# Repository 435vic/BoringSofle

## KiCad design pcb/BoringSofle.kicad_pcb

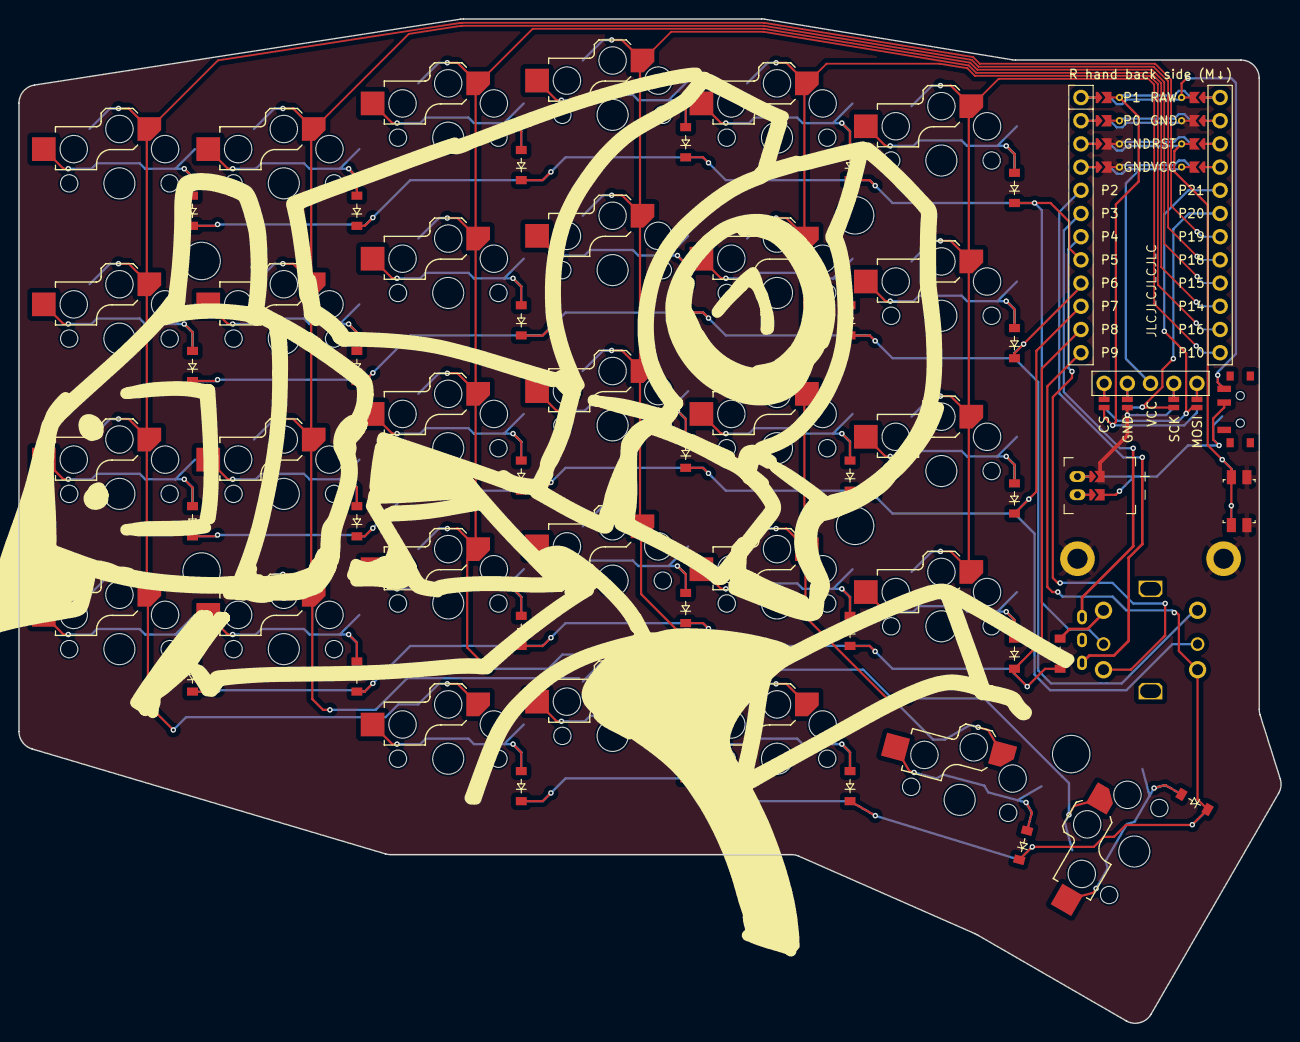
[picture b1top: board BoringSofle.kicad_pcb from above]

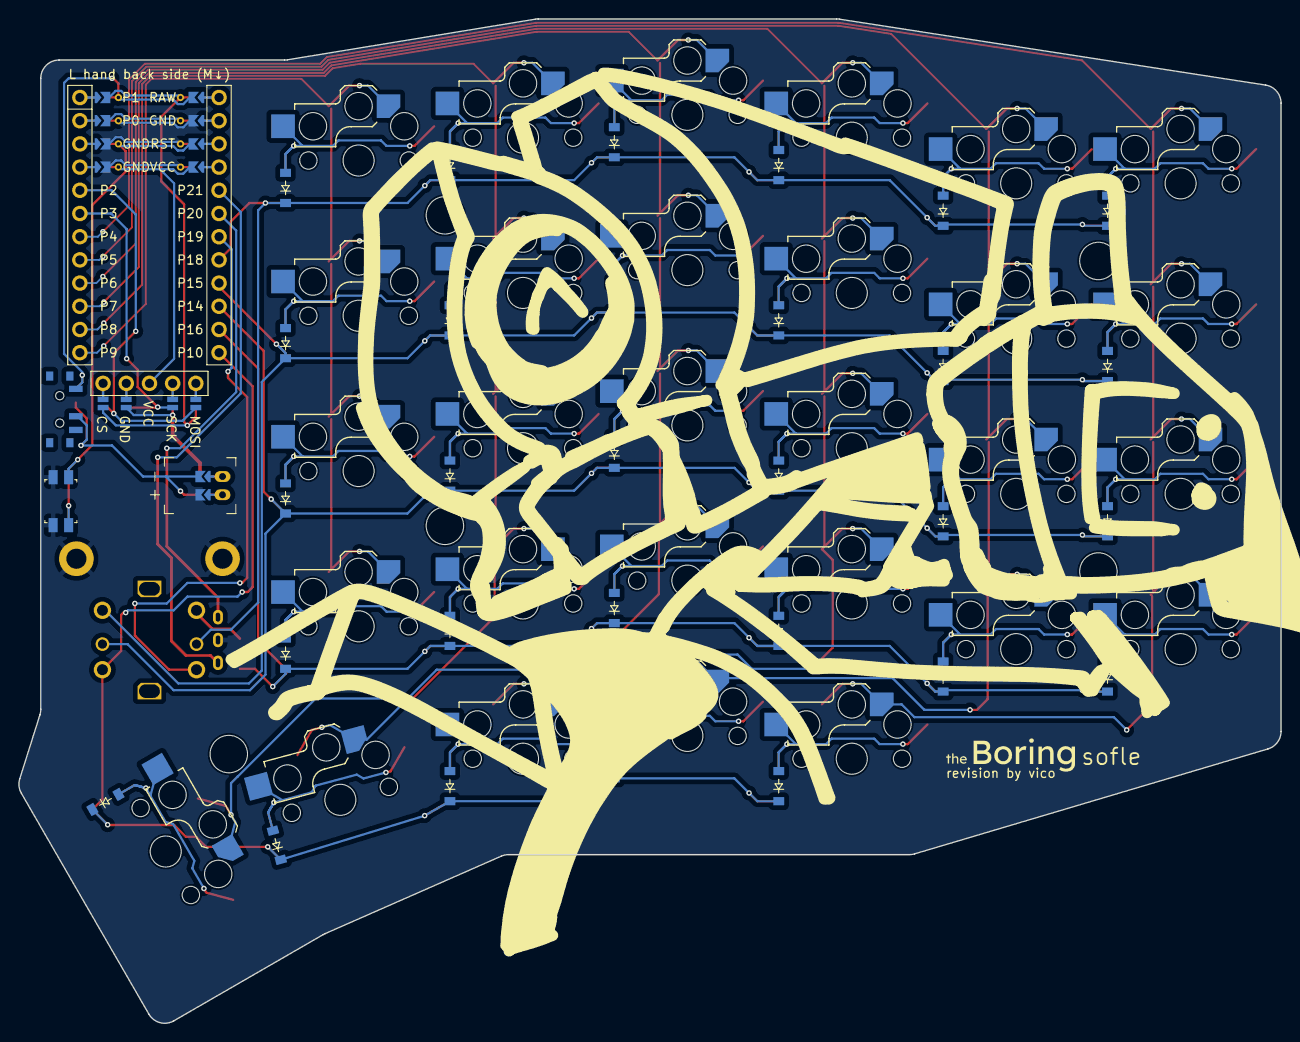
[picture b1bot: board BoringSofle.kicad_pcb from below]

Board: 2 copper layers, 138.2 x 110.0 mm, 73 parts (30 on the bottom side), 58 nets.

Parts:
D1, D2, D3, D4, D5, D6, D7, D8, D9, D10, D11, D12, D13, D14, D15, D16, D17, D18, D19, D20, D21, D22, D23, D24, D25, D26, D27, D28, D29, D30: diode_tht_sod123
DISP1: display_nice_view
H1, H2: mounting_hole_plated
JST1: battery_connector_jst_ph_2
MCU1: mcu_nice_nano
MH1, MH2, MH3, MH4, MH5: mounting_hole_npth
PWR1: power_switch_smd_side
RE1: rotary_encoder_ec11_ec12
RST1: reset_switch_smd_side
S1, S2, S3, S4, S5, S6, S7, S8, S9, S10, S11, S12, S13, S14, S15, S16, S17, S18, S19, S20, S21, S22, S23, S24, S25, S26, S27, S28, S29: switch_choc_v1_v2
SW1: sqku_5way_nav_switch

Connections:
BAT_P: JST1.1, PWR1.2
CS: DISP1.10, DISP1.20, MCU1.124
DISP1_1: DISP1.1, DISP1.14, DISP1.27
DISP1_2: DISP1.2, DISP1.15, DISP1.26
DISP1_4: DISP1.4, DISP1.16, DISP1.25
DISP1_5: DISP1.5, DISP1.17, DISP1.24
GND: DISP1.11, DISP1.21, JST1.2, MCU1.102, MCU1.121, MCU1.122, RE1.B, RST1.1, RST1.3
JST1_1: JST1.11, JST1.21, JST1.31
JST1_2: JST1.12, JST1.22, JST1.32
MOSI: DISP1.13, DISP1.23, MCU1.5
P2: MCU1.20, RE1.A
P3: MCU1.19, RE1.C
P4: MCU1.18, SW1.CMN
P5: D4.1, D8.1, D13.1, D18.1, D23.1, D27.1, MCU1.17, SW1.D
P6: D3.1, D7.1, D12.1, D17.1, D22.1, D26.1, MCU1.16, SW1.A
P7: D2.1, D6.1, D11.1, D16.1, D21.1, D25.1, MCU1.15, SW1.B
P8: D1.1, D5.1, D10.1, D15.1, D20.1, D24.1, D30.1, MCU1.14
P9: D9.1, D14.1, D19.1, D28.1, D29.1, MCU1.13, SW1.C
P10: MCU1.12, S24.1, S25.1, S26.1, S27.1
P14: MCU1.10, S15.1, S16.1, S17.1, S18.1, S28.1
P15: MCU1.9, S10.1, S11.1, S12.1, S13.1, S19.1
P16: MCU1.11, S20.1, S21.1, S22.1, S23.1, S29.1
P18: MCU1.8, S5.1, S6.1, S7.1, S8.1, S14.1
P19: MCU1.7, S1.1, S2.1, S3.1, S4.1, S9.1
RAW: MCU1.101, PWR1.1, PWR1.3
RST: MCU1.103, RST1.2, RST1.4
SCK: DISP1.12, DISP1.22, MCU1.6
VCC: DISP1.3, MCU1.104
index_bottom: D20.2, S20.2
index_home: D21.2, S21.2
index_mod: D19.2, S19.2
index_num: D23.2, S23.2
index_top: D22.2, S22.2
inner_bottom: D24.2, S24.2
inner_home: D25.2, S25.2
inner_num: D27.2, S27.2
inner_top: D26.2, S26.2
layer_cluster: D28.2, S28.2
middle_bottom: D15.2, S15.2
middle_home: D16.2, S16.2
middle_mod: D14.2, S14.2
middle_num: D18.2, S18.2
middle_top: D17.2, S17.2
nav_diode: D30.2, SW1.CTR
outer_bottom: D1.2, S1.2
outer_home: D2.2, S2.2
outer_num: D4.2, S4.2
outer_top: D3.2, S3.2
pinky_bottom: D5.2, S5.2
pinky_home: D6.2, S6.2
pinky_num: D8.2, S8.2
pinky_top: D7.2, S7.2
ring_bottom: D10.2, S10.2
ring_home: D11.2, S11.2
ring_mod: D9.2, S9.2
ring_num: D13.2, S13.2
ring_top: D12.2, S12.2
space_cluster: D29.2, S29.2

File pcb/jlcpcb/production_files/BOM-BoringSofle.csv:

Comment,Designator,Footprint,LCSC,Quantity
,D1,diode_tht_sod123,,1
,D2,diode_tht_sod123,,1
,D3,diode_tht_sod123,,1
,D4,diode_tht_sod123,,1
,D5,diode_tht_sod123,,1
,D6,diode_tht_sod123,,1
,D7,diode_tht_sod123,,1
,D8,diode_tht_sod123,,1
,D9,diode_tht_sod123,,1
,D10,diode_tht_sod123,,1
,D11,diode_tht_sod123,,1
,D12,diode_tht_sod123,,1
,D13,diode_tht_sod123,,1
,D14,diode_tht_sod123,,1
,D15,diode_tht_sod123,,1
,D16,diode_tht_sod123,,1
,D17,diode_tht_sod123,,1
,D18,diode_tht_sod123,,1
,D19,diode_tht_sod123,,1
,D20,diode_tht_sod123,,1
,D21,diode_tht_sod123,,1
,D22,diode_tht_sod123,,1
,D23,diode_tht_sod123,,1
,D24,diode_tht_sod123,,1
,D25,diode_tht_sod123,,1
,D26,diode_tht_sod123,,1
,D27,diode_tht_sod123,,1
,D28,diode_tht_sod123,,1
,D29,diode_tht_sod123,,1
,PWR1,power_switch_smd_side,,1
,RST1,reset_switch_smd_side,,1
,RE1,rotary_encoder_ec11_ec12,,1
,SW1,sqku_5way_nav_switch,,1
,D30,diode_tht_sod123,,1
,H1,mounting_hole_plated,,1
,H2,mounting_hole_plated,,1
,JST1,battery_connector_jst_ph_2,,1
,MH1,mounting_hole_npth,,1
,MH2,mounting_hole_npth,,1
,MH3,mounting_hole_npth,,1
,MH4,mounting_hole_npth,,1
,MH5,mounting_hole_npth,,1

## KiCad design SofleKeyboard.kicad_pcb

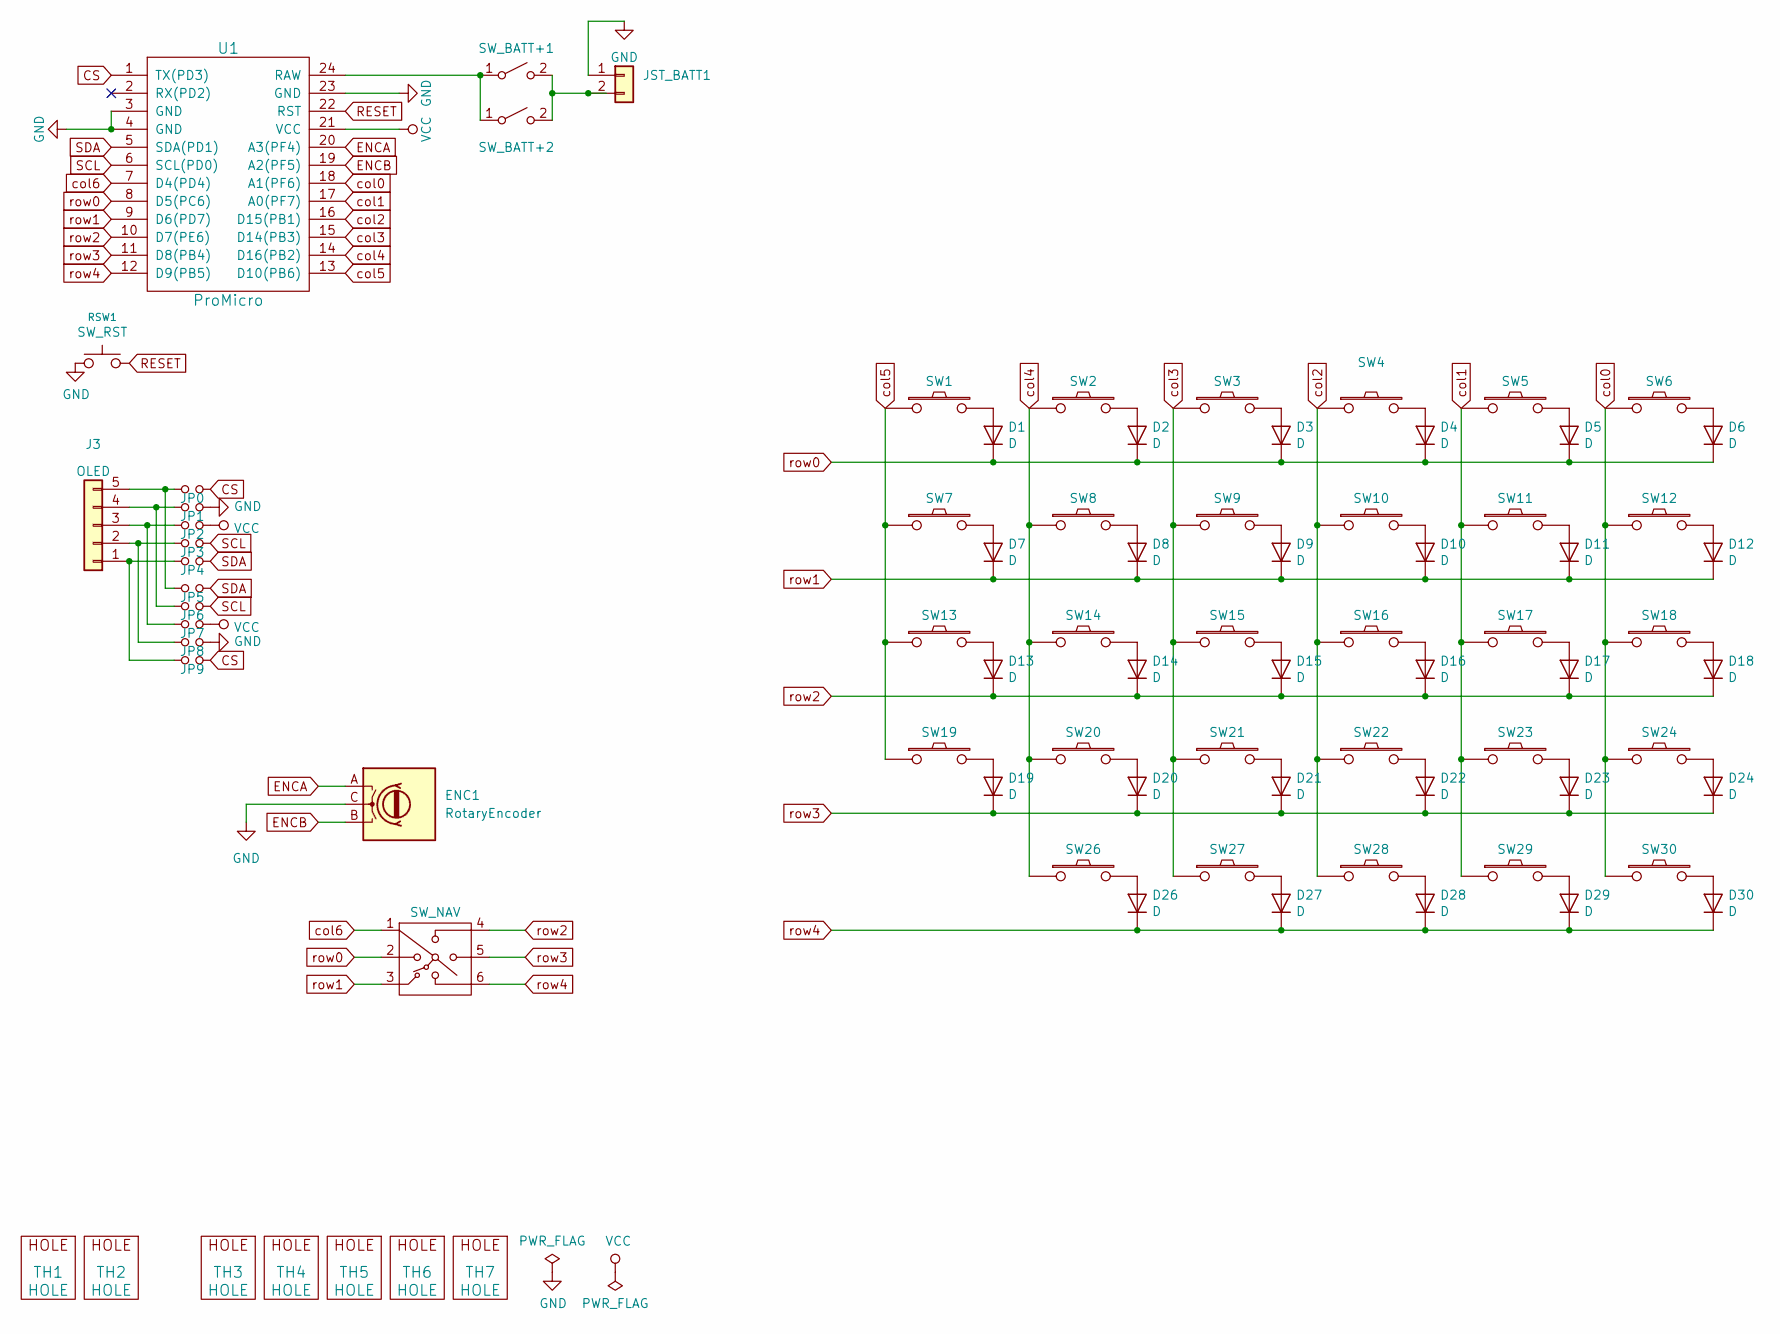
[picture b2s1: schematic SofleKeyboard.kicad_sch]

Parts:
D1, D2, D3, D4, D5, D6, D7, D8, D9, D10, D11, D12, D13, D14, D15, D16, D17, D18, D19, D20, D21, D22, D23, D24, D26, D27, D28, D29, D30: D; crkbd-diode
ENC1: RotaryEncoder; RotaryEncoder_Alps_EC12E_Vertical_H20mm
J3: OLED; OLED_NICEVIEW_COMBO_HDR_5Pin
JP0, JP1, JP2, JP3, JP4, JP5, JP6, JP7, JP8, JP9: Jumper_NO_Small; Jumper_small
JST_BATT1: Conn_01x02; JST_PH_S2B-PH-K_1x02_P2.00mm_DoubleSided
RSW1: SW_RST; Panasonic_EVQPUL_EVQPUC
SW1, SW7, SW13, SW19: SW_PUSH_LED; Choc_Hotswap_BiggerHSPads_Column1
SW2, SW3, SW4, SW5, SW6, SW8, SW9, SW10, SW11, SW12, SW14, SW15, SW16, SW17, SW18, SW20, SW21, SW22, SW23, SW24, SW26, SW27, SW28, SW29, SW30: SW_PUSH_LED; Choc_Hotswap_BiggerHSPads
SW_BATT+1, SW_BATT+2: SW_SPST; SW_SPDT_PCM12
SW_NAV_1: SW_NAV; NavSwitch_5Way
TH1, TH2: HOLE; M2_HOLE_PCB
TH3, TH4, TH5, TH6, TH7: HOLE; HOLE_M2_TH
U1: ProMicro

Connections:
CS: JP0.2, JP9.2, U1.1 (TX(PD3))
ENCA: ENC1.A, U1.20 (A3(PF4))
ENCB: ENC1.B, U1.19 (A2(PF5))
GND: ENC1.C, JP1.2, JP8.2, JST_BATT1.1, RSW1.1, U1.3 (GND), U1.4 (GND), U1.23 (GND)
unnamed: D1.2 (A), SW1.5
unnamed: D2.2 (A), SW2.5
unnamed: D3.2 (A), SW3.5
unnamed: D4.2 (A), SW4.5
unnamed: D5.2 (A), SW5.5
unnamed: D6.2 (A), SW6.5
unnamed: D7.2 (A), SW7.5
unnamed: D8.2 (A), SW8.5
unnamed: D9.2 (A), SW9.5
unnamed: D10.2 (A), SW10.5
unnamed: D11.2 (A), SW11.5
unnamed: D12.2 (A), SW12.5
unnamed: D13.2 (A), SW13.5
unnamed: D14.2 (A), SW14.5
unnamed: D15.2 (A), SW15.5
unnamed: D16.2 (A), SW16.5
unnamed: D17.2 (A), SW17.5
unnamed: D18.2 (A), SW18.5
unnamed: D19.2 (A), SW19.5
unnamed: D20.2 (A), SW20.5
unnamed: D21.2 (A), SW21.5
unnamed: D22.2 (A), SW22.5
unnamed: D23.2 (A), SW23.5
unnamed: D24.2 (A), SW24.5
unnamed: D26.2 (A), SW26.5
unnamed: D27.2 (A), SW27.5
unnamed: D28.2 (A), SW28.5
unnamed: D29.2 (A), SW29.5
unnamed: D30.2 (A), SW30.5
unnamed: J3.1, JP4.1, JP9.1
unnamed: J3.2, JP3.1, JP8.1
unnamed: J3.3, JP2.1, JP7.1
unnamed: J3.4, JP1.1, JP6.1
unnamed: J3.5, JP0.1, JP5.1
unnamed: JST_BATT1.2, SW_BATT+1.2 (B), SW_BATT+2.2 (B)
unnamed: SW_BATT+1.1 (A), SW_BATT+2.1 (A), U1.24 (RAW)
RESET: RSW1.2, U1.22 (RST)
SCL: JP3.2, JP6.2, U1.6 (SCL(PD0))
SDA: JP4.2, JP5.2, U1.5 (SDA(PD1))
VCC: JP2.2, JP7.2, U1.21 (VCC)
col0: SW6.6, SW12.6, SW18.6, SW24.6, SW30.6, U1.18 (A1(PF6))
col1: SW5.6, SW11.6, SW17.6, SW23.6, SW29.6, U1.17 (A0(PF7))
col2: SW4.6, SW10.6, SW16.6, SW22.6, SW28.6, U1.16 (D15(PB1))
col3: SW3.6, SW9.6, SW15.6, SW21.6, SW27.6, U1.15 (D14(PB3))
col4: SW2.6, SW8.6, SW14.6, SW20.6, SW26.6, U1.14 (D16(PB2))
col5: SW1.6, SW7.6, SW13.6, SW19.6, U1.13 (D10(PB6))
col6: SW_NAV_1.1, U1.7 (D4(PD4))
row0: D1.1 (K), D2.1 (K), D3.1 (K), D4.1 (K), D5.1 (K), D6.1 (K), SW_NAV_1.2, U1.8 (D5(PC6))
row1: D7.1 (K), D8.1 (K), D9.1 (K), D10.1 (K), D11.1 (K), D12.1 (K), SW_NAV_1.3, U1.9 (D6(PD7))
row2: D13.1 (K), D14.1 (K), D15.1 (K), D16.1 (K), D17.1 (K), D18.1 (K), SW_NAV_1.4, U1.10 (D7(PE6))
row3: D19.1 (K), D20.1 (K), D21.1 (K), D22.1 (K), D23.1 (K), D24.1 (K), SW_NAV_1.5, U1.11 (D8(PB4))
row4: D26.1 (K), D27.1 (K), D28.1 (K), D29.1 (K), D30.1 (K), SW_NAV_1.6, U1.12 (D9(PB5))

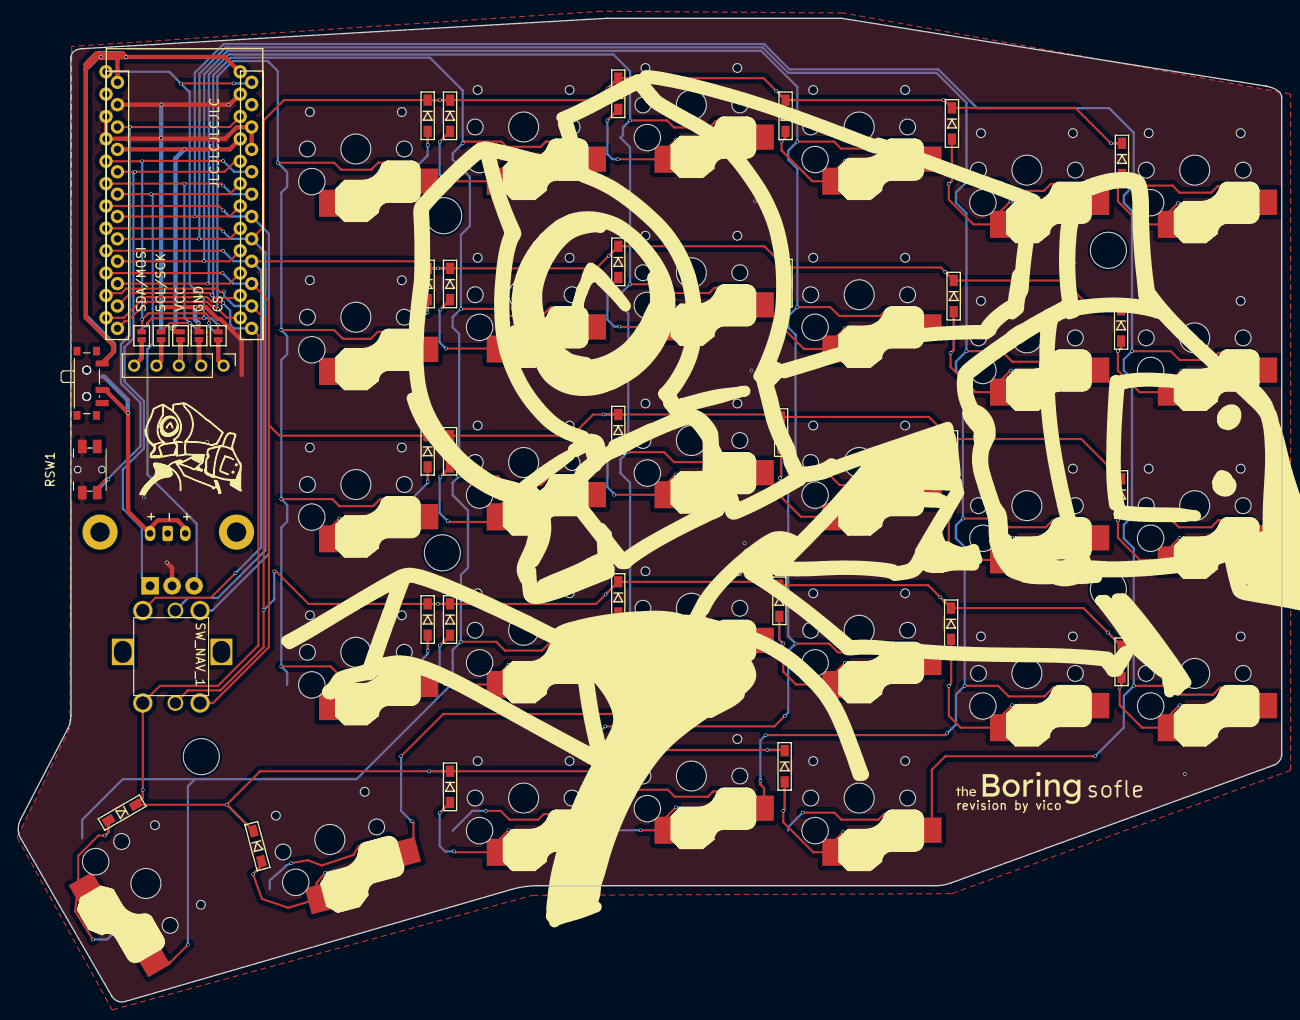
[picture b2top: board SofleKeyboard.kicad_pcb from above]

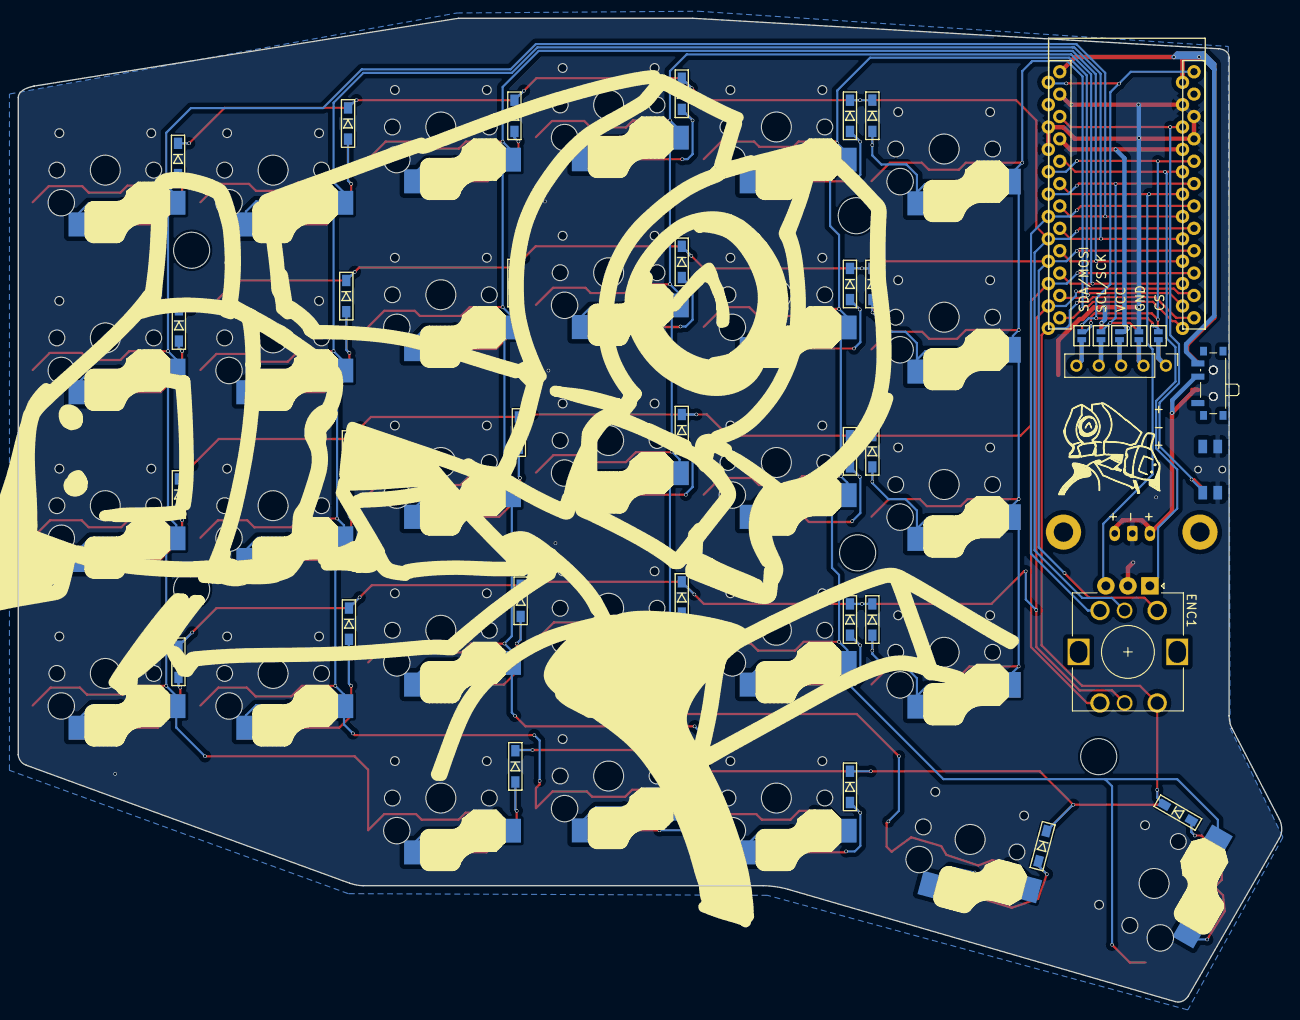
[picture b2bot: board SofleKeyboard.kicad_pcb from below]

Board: 2 copper layers, 143.5 x 111.7 mm, 83 parts (7 on the bottom side), 56 nets.

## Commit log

2025-04-09 original soflechocwireless
2025-04-09 first stage: schematic and pcb footprints
2025-04-09 add sofle library, pcb outline, link new footprints to pcb
2025-04-12 jlc rules, add board outline in edge.cuts
2025-04-12 change board outline
2025-04-13 update jlcpcb constraints
2025-04-13 update diode footprint, add ground zones, start board routing
2025-04-13 wire columns 5, 4, 3 and 2
2025-04-14 first iteration done
2025-04-14 add license
2025-05-17 change pushbutton footprint, misc changes
2025-07-15 add branding and logo
2025-07-15 update constraints, switch to 0.127mm track clearance
2025-07-31 some stuff
2025-08-02 add pcb definition
2025-08-02 add nix shell for ergogen
2025-08-02 Squashed 'ergogen/footprints/ceoloide/' content from commit 2d62ba4
    git-subtree-dir: ergogen/footprints/ceoloide
    git-subtree-split: 2d62ba49e8f41255735f0339459420685c65aac2
2025-08-02 add nice view footprint
2025-08-02 add side-agnostic components
2025-08-02 add zone fill
2025-08-03 add more footprints
2025-08-03 setup nets, finalize outlines, nearing completion
2025-08-04 tweak jst ph jumpers for proper zone fills
2025-08-04 add 5 way nav switch
2025-08-04 add diode and proper nets to nav switch
2025-08-04 add 3d models
2025-08-05 add almost all routing through ergogen
2025-08-05 fully route board through ergogen
2025-08-05 adjust mounting holes
2025-08-05 add final pcb files and gerbers
2025-08-05 adjust encoder positions and plate
2025-08-05 update kicad project pcbs
2025-08-06 shift encoder position and rotation, redesign top plate
